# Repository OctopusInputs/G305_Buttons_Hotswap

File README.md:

# G305_Buttons_Hotswap
 Hotswap switch PCBs for the G305 using Mill-Max 7305 sockets

Requires: 

Mill-Max 7305 sockets, JST SH 4pin Male Connector

0.8mm board height for the original PCB height

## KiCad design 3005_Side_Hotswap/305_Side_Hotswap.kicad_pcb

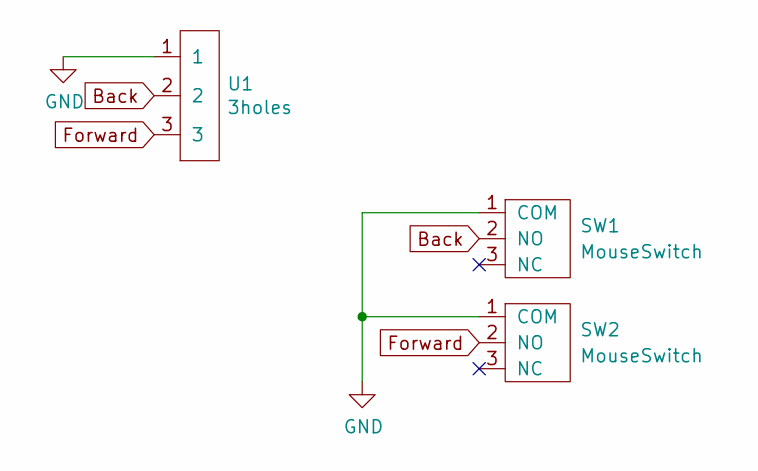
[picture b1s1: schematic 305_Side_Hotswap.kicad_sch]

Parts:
SW1, SW2: MouseSwitch; 7305 Socket
U1: 3holes

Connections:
Back: SW1.2 (NO), U1.2
Forward: SW2.2 (NO), U1.3
GND: SW1.1 (COM), SW2.1 (COM), U1.1

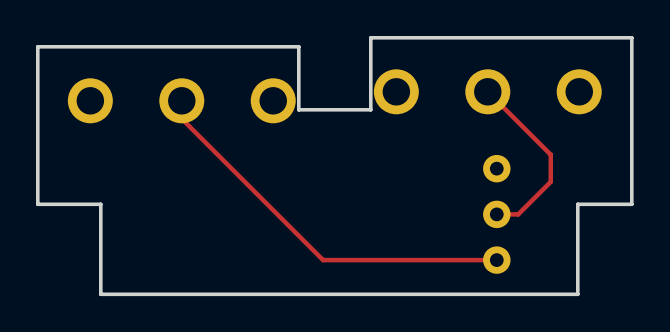
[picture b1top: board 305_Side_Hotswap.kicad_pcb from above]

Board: 2 copper layers, 33.0 x 14.2 mm, 3 parts (1 on the bottom side), 3 nets.
